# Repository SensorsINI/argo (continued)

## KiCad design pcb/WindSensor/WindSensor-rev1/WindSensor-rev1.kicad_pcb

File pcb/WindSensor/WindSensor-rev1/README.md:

# Argo Wind Sensor - Revision 1

## Overview

This is the first revision (Rev 1) of the Argo Wind Sensor PCB. The board is designed to measure wind speed and direction for the Argo sailboat. 

It is based on Sensiorion reference design (since removed from sensorion because the page could not be migrated). Sensirion kindly supplied the step file as a starting point for the current design. The current design is combined with a mast mounting part that clamps to the mast backstay carbon fiber part.

The PCB design includes 3 SDP32 differential pressure sensors and 
an RGBW LED controller with RGBW LED. Sensors and LED controller are on the Argo I2C bus and are connected to Argo's computer via the 4-wire cable through the Molex SL-series SMD header. The mast mount part includes a set screw to provide strain relief for the SMD Molex header.

The PCB was designed in Kicad 9. The housing was designed in FreeCAD 1.1rc2.

The PCB was fabricated by JLCPCB.

See the argo ROS2 nodes anem.py and mastled.py for sensing and control of the wind sensor.

## Specifications

### Electrical
- **Supply Voltage**: 5V
- **Operating Current**: ~160mA max (3 LEDS, each max 50mA)~
- **Communication Interface**: I2C

### Physical
- **Board Dimensions**: 20x20mm
- **Number of Layers**: 2
- **Surface Finish**: ENIG

## Design Files

This directory contains:
- Schematic files (`.kicad_sch` Kicad Version 9)
- PCB layout files (`.kicad_pcb` )
- 3D models (if applicable)

## Bill of Materials (BOM)

The BOM is generated from Kicad
Parts include datasheet links and Digikey or Farnell part links.

## Manufacturing

### Gerber Files
Gerber files are generated from kicad in the `gerbers/` directory. These can be sent directly to a PCB manufacturer.

### Fabrication Notes
- Minimum trace width: 0.2mm
- Minimum via size: 0.3mm

## Known Issues

- None currently documented for Rev 1

## Revision History

### Rev 1 (Initial Release)
- Initial PCB design
- Date: TBD

### Rev 0 (initial design done by ETH semester student Andrea Mock, ca 2019)

## Contact

For questions or issues related to this PCB design, please contact Tobi Delbruck.

## License

LGPLv3

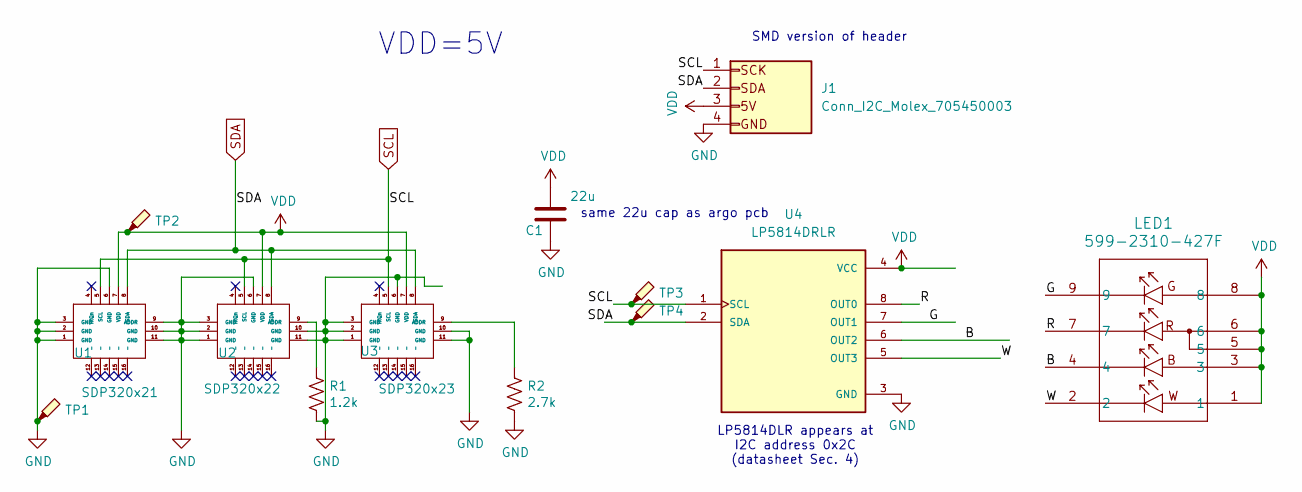
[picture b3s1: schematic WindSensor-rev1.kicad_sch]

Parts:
C1: 22u; C_1210_3225Metric_Pad1.33x2.70mm_HandSolder
J1: Conn_I2C_Molex_705450003; CONN_SD-74099-1000_04_MOL
LED1: 599-2310-427F; 599-2310_DIA_hand_solder
R1: 1.2k; R_0603_1608Metric_Pad0.98x0.95mm_HandSolder
R2: 2.7k; R_0603_1608Metric_Pad0.98x0.95mm_HandSolder
TP1, TP2, TP3, TP4: TestPoint_Probe_autonamed; TestPoint_scope_probe_autonamed
U1: SDP320x21; SDP32
U2: SDP320x22; SDP32
U3: SDP320x23; SDP32
U4: LP5814DRLR; IC_LP5814DRLR_hand_solder; PARTREV MARCH 2025; DigiKey_Part_Number 296-LP5814DRLRCT-ND

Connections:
/B: LED1.4, U4.6 (OUT2)
/G: LED1.9, U4.7 (OUT1)
/R: LED1.7, U4.8 (OUT0)
/W: LED1.2, U4.5 (OUT3)
GND: C1.1, J1.4 (GND), R1.2, R2.2, TP1.1, U1.1 (GND), U1.2 (GND), U1.3 (GND), U1.6 (GND), U1.9 (ADDR), U1.10 (GND), U1.11 (GND), U1.17 (GND), U1.18 (GND), U2.1 (GND), U2.2 (GND), U2.3 (GND), U2.6 (GND), U2.10 (GND), U2.11 (GND), U2.17 (GND), U2.18 (GND), U3.1 (GND), U3.2 (GND), U3.3 (GND), U3.6 (GND), U3.10 (GND), U3.11 (GND), U3.17 (GND), U3.18 (GND), U4.3 (GND)
unnamed: R1.1, U2.9 (ADDR)
unnamed: R2.1, U3.9 (ADDR)
SCL: J1.1 (SCLK), TP3.1, U1.5 (SCL), U2.5 (SCL), U3.5 (SCL), U4.1 (SCL)
SDA: J1.2 (SDA), TP4.1, U1.8 (SDA), U2.8 (SDA), U3.8 (SDA), U4.2 (SDA)
VDD: C1.2, J1.3 (5V), LED1.1, LED1.3, LED1.5, LED1.6, LED1.8, TP2.1, U1.7 (VDD), U2.7 (VDD), U3.7 (VDD), U4.4 (VCC)

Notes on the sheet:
VDD=5V
same 22u cap as argo pcb
LP5814DLR appears at I2C address 0x2C (datasheet Sec. 4)
SMD version of header

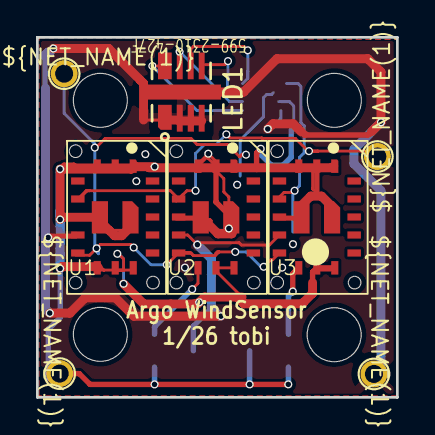
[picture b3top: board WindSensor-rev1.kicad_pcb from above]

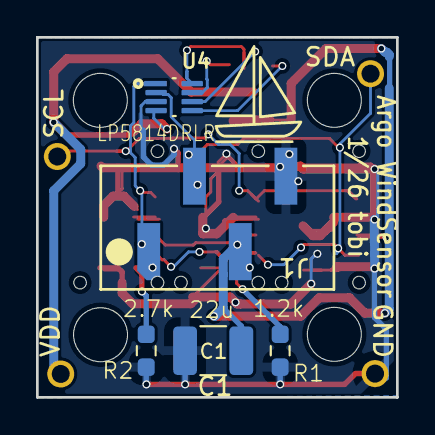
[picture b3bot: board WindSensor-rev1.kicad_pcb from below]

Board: 2 copper layers, 20.0 x 20.0 mm, 17 parts (5 on the bottom side), 10 nets.

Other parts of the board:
H1, H2, H3, H4: (no value)

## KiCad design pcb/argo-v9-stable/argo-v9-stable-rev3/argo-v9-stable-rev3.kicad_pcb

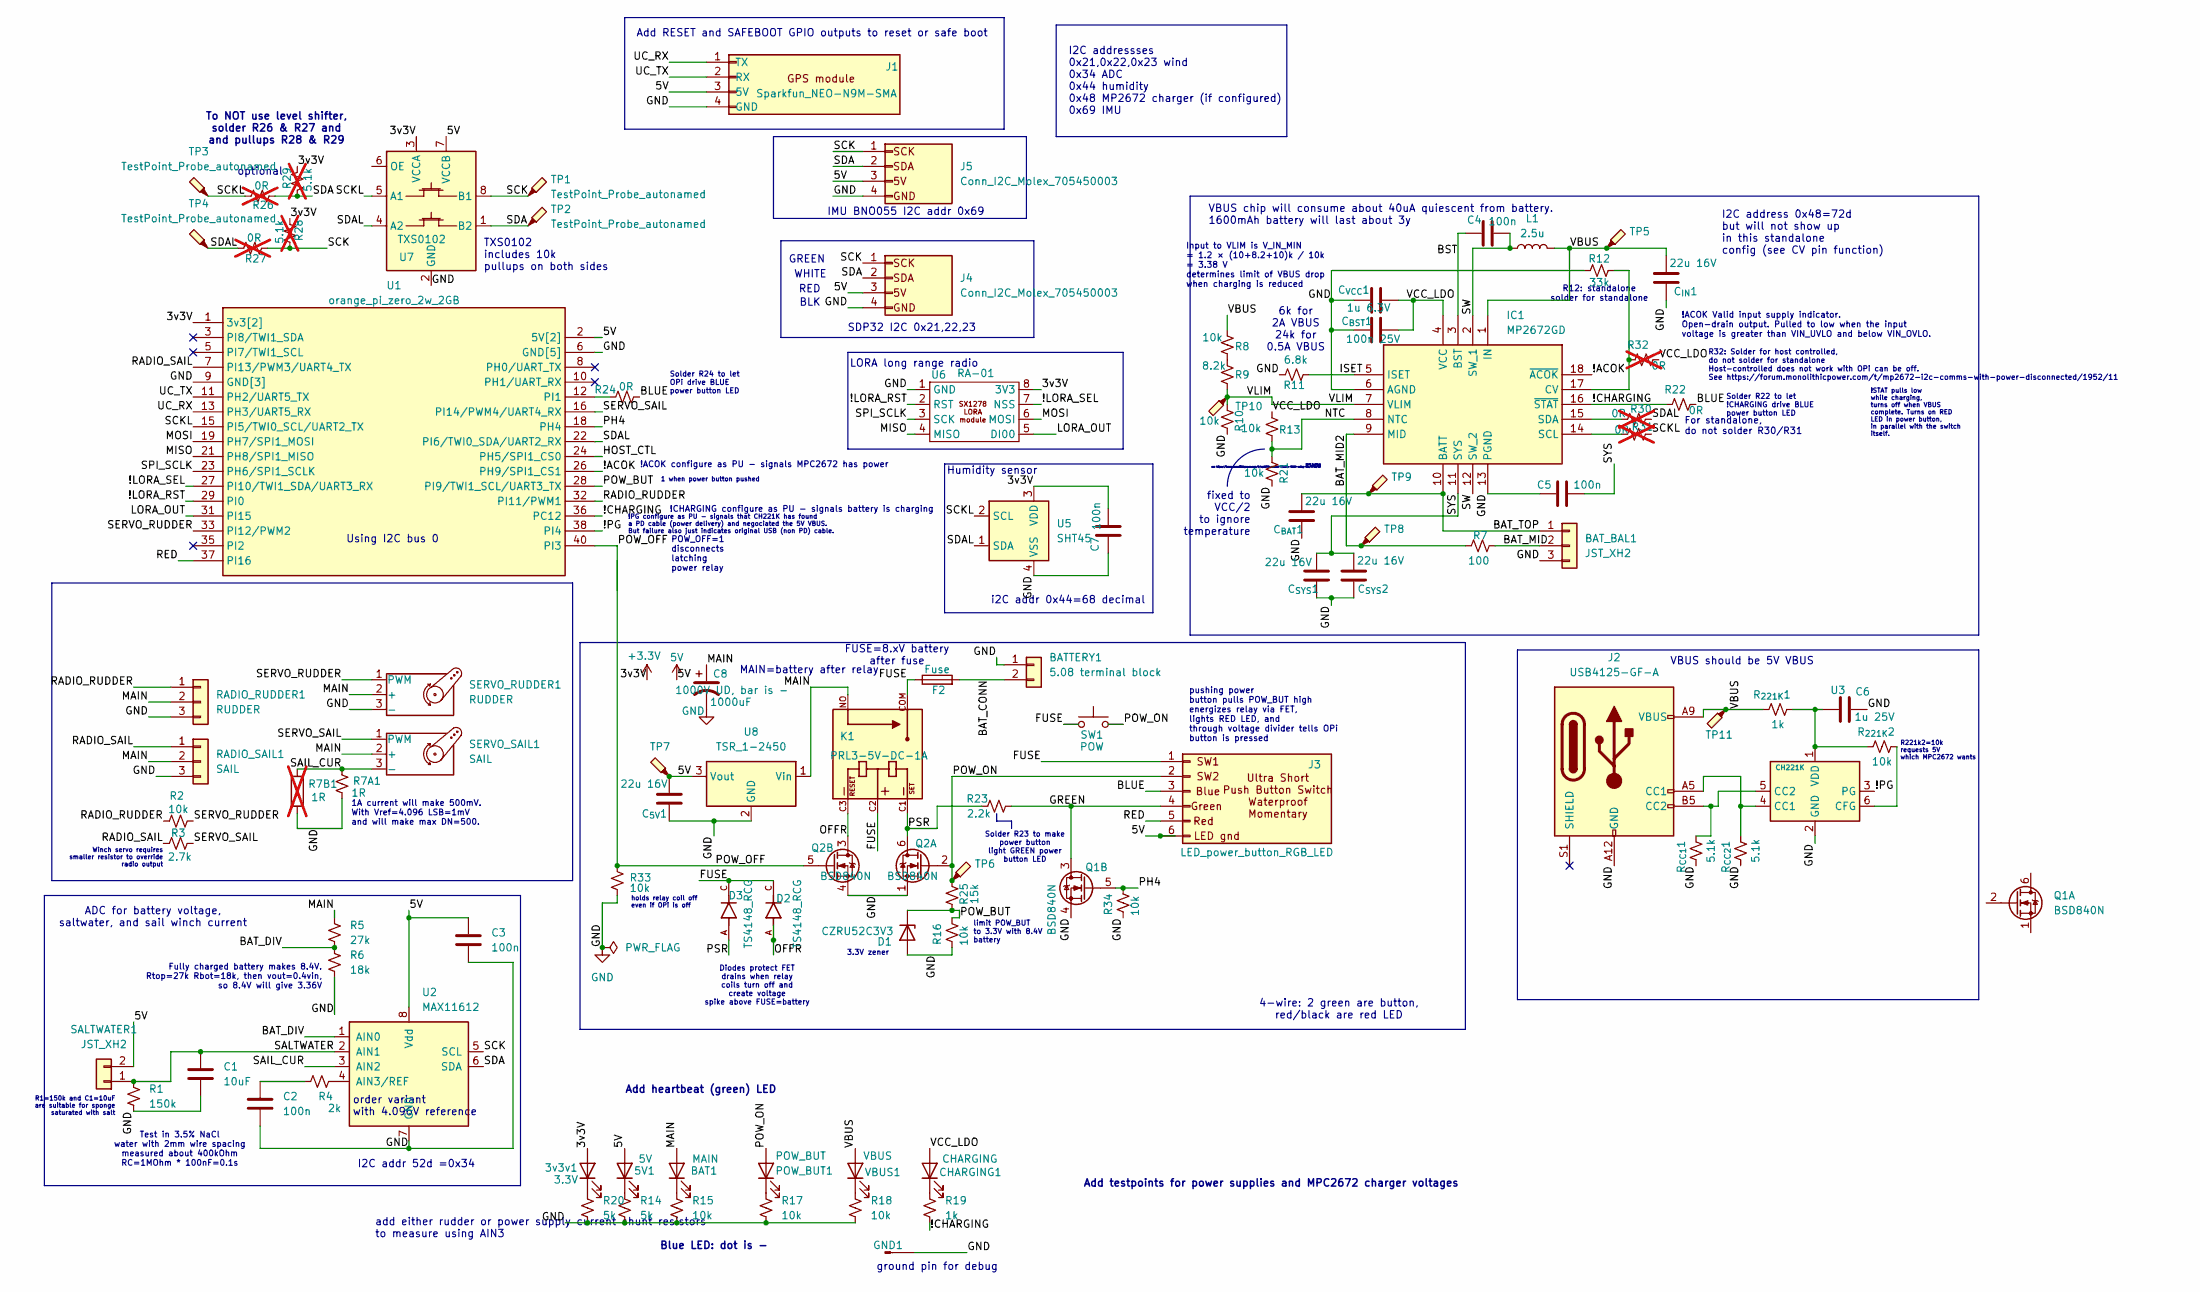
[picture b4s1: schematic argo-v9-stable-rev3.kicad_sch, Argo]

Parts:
3v3v1: 3.3V; LED_0603_1608Metric_Pad1.05x0.95mm_HandSolder
5V1: 5V; LED_0603_1608Metric_Pad1.05x0.95mm_HandSolder
BAT1: MAIN; LED_0603_1608Metric_Pad1.05x0.95mm_HandSolder
BATTERY1: 5.08 terminal block; TerminalBlock_Phoenix_MKDS-1,5-2-5.08_1x02_P5.08mm_Horizont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
BAT_BAL1: JST_XH2; JST_XH_S3B-XH-A-1_1x03_P2.50mm_Horizontal
C1: 10uF; C_0603_1608Metric_Pad1.08x0.95mm_HandSolder
C2, C3, C4, C5, C7: 100n; C_0603_1608Metric_Pad1.08x0.95mm_HandSolder
C6: 1u 25V; C_0603_1608Metric_Pad1.08x0.95mm_HandSolder
C8: 1000uF; PCAP_10x10-ELECT_NCA; digikey have 4 in lab
CHARGING1: CHARGING; LED_0603_1608Metric_Pad1.05x0.95mm_HandSolder
C_{5V}1: 22u 16V; C_1210_3225Metric_Pad1.33x2.70mm_HandSolder
C_{BAT}1: 22u 16V; C_1210_3225Metric_Pad1.33x2.70mm_HandSolder
C_{BST}1: 100n 25V; C_0603_1608Metric_Pad1.08x0.95mm_HandSolder
C_{IN}1: 22u 16V; C_1210_3225Metric_Pad1.33x2.70mm_HandSolder
C_{SYS}1, C_{SYS}2: 22u 16V; C_1210_3225Metric_Pad1.33x2.70mm_HandSolder
C_{VCC}1: 1u 6.3V; C_0603_1608Metric_Pad1.08x0.95mm_HandSolder
D1: CZRU52C3V3; D_0603_1608Metric_hand_solder
D2, D3: TS4148_RCG; DIO_TS4148_RCG; PARTREV A2301
F2: Fuse; Fuse_Smd- Nano SMF AliExp
GND1: Conn_01x01_Pin; Pin_D1.0mm_L10.0mm_LooseFit
IC1: MP2672GD; QFN40P200X300X100-18N-D-handsolder; Manufacturer_Part_Number MP2672GD-0000
J1: Sparkfun_NEO-N9M-SMA; Sparkfun_NEO-M9N-SMA
J2: USB4125-GF-A; USB_C_Receptacle_GCT_USB4125-xx-x-0190_6P_TopMnt_Horizontal
J3: LED_power_button_RGB_LED; JST_XH_S6B-XH-A_1x06_P2.50mm_Horizontal
J4, J5: Conn_I2C_Molex_705450003; I2C_header
K1: PRL3-5V-DC-1A; RELAY_PRL3-5V-DC-1A; PARTREV 1.0
L1: 2.5u; L_Aliexpress_2.5uH
POW_BUT1: POW_BUT; LED_0603_1608Metric_Pad1.05x0.95mm_HandSolder
Q1: BSD840N; SOT-363_SC-70-6
Q2: BSD840N; SOT-363_SC-70-6-handsolder
R1: 150k; R_0603_1608Metric_Pad0.98x0.95mm_HandSolder
R2, R8, R10, R13, R15, R16, R17, R18, R21, R33, R34: 10k; R_0603_1608Metric_Pad0.98x0.95mm_HandSolder
R3: 2.7k; R_0603_1608Metric_Pad0.98x0.95mm_HandSolder
R4: 2k; R_0603_1608Metric_Pad0.98x0.95mm_HandSolder
R5: 27k; R_0603_1608Metric_Pad0.98x0.95mm_HandSolder
R6: 18k; R_0603_1608Metric_Pad0.98x0.95mm_HandSolder
R7: 100; R_0603_1608Metric_Pad0.98x0.95mm_HandSolder
R7A1: 1R; R_0603_1608Metric_Pad0.98x0.95mm_HandSolder
R7B1: 1R; R_Axial_DIN0204_L3.6mm_D1.6mm_P2.54mm_Vertical; not fitted
R9: 8.2k; R_0603_1608Metric_Pad0.98x0.95mm_HandSolder
R11: 6.8k; R_0603_1608Metric_Pad0.98x0.95mm_HandSolder
R12: 33k; R_0603_1608Metric_Pad0.98x0.95mm_HandSolder
R14, R20: 5k; R_0603_1608Metric_Pad0.98x0.95mm_HandSolder
R19: 1k; R_0603_1608Metric_Pad0.98x0.95mm_HandSolder
R22, R24: 0R; R_0603_1608Metric_Pad0.98x0.95mm_HandSolder
R23: 2.2k; R_0603_1608Metric_Pad0.98x0.95mm_HandSolder
R25: 15k; R_0603_1608Metric_Pad0.98x0.95mm_HandSolder
R26, R27, R30, R31, R32: 0R; R_0603_1608Metric_Pad0.98x0.95mm_HandSolder; not fitted
R28, R29: 5.1k; R_0603_1608Metric_Pad0.98x0.95mm_HandSolder; not fitted
RADIO_RUDDER1: RUDDER; PinHeader_1x03_P2.54mm_Vertical
RADIO_SAIL1: SAIL; PinHeader_1x03_P2.54mm_Vertical
R_{221K}1: 1k; R_0603_1608Metric_Pad0.98x0.95mm_HandSolder
R_{221K}2: 10k; R_0603_1608Metric_Pad0.98x0.95mm_HandSolder
R_{CC1}1, R_{CC2}1: 5.1k; R_0603_1608Metric_Pad0.98x0.95mm_HandSolder
SALTWATER1: JST_XH2; JST_XH_S2B-XH-A_1x02_P2.50mm_Horizontal
SERVO_RUDDER1: RUDDER; PinHeader_1x03_P2.54mm_Vertical
SERVO_SAIL1: SAIL; PinHeader_1x03_P2.54mm_Vertical
SW1: POW; SW_Tactile_SPST_NO_Straight_CK_PTS636Sx25SMTRLFS
TP1, TP2, TP3, TP4, TP5, TP6, TP7, TP8, TP9, TP10, TP11: TestPoint_Probe_autonamed; TestPoint_scope_probe_autonamed
U1: orange_pi_zero_2w_2GB; orange_pi_zero_2w_butted
U2: MAX11612; MSOP-8_3x3mm_P0.65mm
U3: CH221K; TSOT-23-6_HandSoldering
U5: SHT45; Sensirion_DFN-4_1.5x1.5mm_P0.8mm_SHT4x_NoCentralPad-handsol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
U6: RA-01; RA-01 SX1278 LORA
U7: TXS0102; SSOP-8_2.95x2.8mm_P0.65mm
U8: TSR_1-2450; Converter_DCDC_TRACO_TSR1-xxxxE_THT
VBUS1: VBUS; LED_0603_1608Metric_Pad1.05x0.95mm_HandSolder

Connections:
5V: 5V1.2 (A), C3.1, C_{5V}1.2, J1.3 (5V), J3.6, J4.3 (5V), J5.3 (5V), SALTWATER1.2, TP7.1, U1.2 (5V[2]), U1.4 (5V[2]), U2.8 (Vdd), U7.7 (VCCB), U8.3 (Vout)
+3.3V: 3v3v1.2 (A), C7.2, R28.2, R29.2, U1.1 (3v3[2]), U1.17 (3v3[2]), U5.3 (VDD), U6.8 (3V3), U7.3 (VCCA)
/!ACOK: IC1.18 (~ACOK), U1.26 (PH9/SPI1_CS1)
/!CHARGING: IC1.16 (~STAT), R19.2, R22.1, U1.36 (PC12)
/!LORA_RST: U1.29 (PI0), U6.2 (RST)
/!LORA_SEL: U1.27 (PI10/TWI1_SDA/UART3_RX), U6.7 (NSS)
/!PG: U1.38 (PI4), U3.3 (PG)
/BAT_CONN: BATTERY1.2, F2.2
/BAT_DIV: R5.2, R6.1, U2.1 (AIN0)
/BAT_MID: BAT_BAL1.2, R7.1
/BAT_MID2: IC1.9 (MID), R7.2, TP8.1
/BAT_TOP: BAT_BAL1.1, C_{BAT}1.2, IC1.10 (BATT), TP9.1
/BLUE: J3.3, R22.2, R24.2
/BST: C4.1, IC1.3 (BST)
/FUSE: D2.C, D3.C, F2.1, J3.1, K1.C2, K1.COM, SW1.1
/GREEN: J3.4, Q1.3 (D), R23.2
/HOST_CTL: U1.24 (PH5/SPI1_CS0)
/LORA_OUT: U1.31 (PI15), U6.5 (DI00)
/MAIN: BAT1.2 (A), C8.1, K1.NO, R5.1, RADIO_RUDDER1.2, RADIO_SAIL1.2, SERVO_RUDDER1.2 (+), SERVO_SAIL1.2 (+), U8.1 (Vin)
/MISO: U1.21 (PH8/SPI1_MISO), U6.4 (MISO)
/MOSI: U1.19 (PH7/SPI1_MOSI), U6.6 (MOSI)
/OFFR: D2.A, K1.C3, Q2.3 (D)
/PH4: Q1.5 (G), R34.2, U1.18 (PH4)
/POW_BUT: D1.1 (K), R16.2, R25.1, U1.28 (PI9/TWI1_SCL/UART3_TX)
/POW_OFF: Q2.5 (G), R33.1, U1.40 (PI3)
/POW_ON: J3.2, POW_BUT1.2 (A), Q2.2 (G), R25.2, SW1.2, TP6.1
/PSR: D3.A, K1.C1, Q2.6 (D), R23.1
/RADIO_RUDDER: R2.1, RADIO_RUDDER1.1, U1.32 (PI11/PWM1)
/RADIO_SAIL: R3.1, RADIO_SAIL1.1, U1.7 (PI13/PWM3/UART4_TX)
/RED: J3.5, U1.37 (PI16)
/SAIL_CUR: R7A1.1, R7B1.1, SERVO_SAIL1.3 (-), U2.3 (AIN2)
/SALTWATER: C1.1, R1.1, SALTWATER1.1, U2.2 (AIN1)
/SCK: J4.1 (SCLK), J5.1 (SCLK), R27.2, R28.1, TP1.1, U2.5 (SCL), U7.8 (B1)
/SCKL: R26.1, R31.2, TP3.1, U1.15 (PI5/TWI0_SCL/UART2_TX), U5.2 (SCL), U7.5 (A1)
/SDA: J4.2 (SDA), J5.2 (SDA), R26.2, R29.1, TP2.1, U2.6 (SDA), U7.1 (B2)
/SDAL: R27.1, R30.2, TP4.1, U1.22 (PI6/TWI0_SDA/UART2_RX), U5.1 (SDA), U7.4 (A2)
/SERVO_RUDDER: R2.2, SERVO_RUDDER1.1 (PWM), U1.33 (PI12/PWM2)
/SERVO_SAIL: R3.2, SERVO_SAIL1.1 (PWM), U1.16 (PI14/PWM4/UART4_RX)
/SPI_SCLK: U1.23 (PH6/SPI1_SCLK), U6.3 (SCK)
/SW: C4.2, IC1.2 (SW_1), IC1.12 (SW_2), L1.1
/SYS: C5.2, C_{SYS}1.2, C_{SYS}2.2, IC1.11 (SYS)
/UC_RX: J1.1 (TX), U1.13 (PH3/UART5_RX)
/UC_TX: J1.2 (RX), U1.11 (PH2/UART5_TX)
/VBUS: C_{IN}1.2, IC1.1 (IN), J2.A9 (VBUS), J2.B9 (VBUS), L1.2, R8.1, R_{221K}1.1, TP5.1, TP11.1, VBUS1.2 (A)
/VCC_LDO: CHARGING1.2 (A), C_{BST}1.2, C_{VCC}1.2, IC1.4 (VCC), R13.1, R32.2
/VLIM: IC1.7 (VLIM), R9.2, R10.1, TP10.1
GND: BATTERY1.1, BAT_BAL1.3, C1.2, C2.2, C3.2, C5.1, C6.2, C7.1, C8.2, C_{5V}1.1, C_{BAT}1.1, C_{BST}1.1, C_{IN}1.1, C_{SYS}1.1, C_{SYS}2.1, C_{VCC}1.1, D1.2 (A), GND1.1, IC1.6 (AGND), IC1.13 (PGND), J1.4 (GND), J2.A12 (GND), J2.B12 (GND), J4.4 (GND), J5.4 (GND), Q1.4 (S), Q2.1 (S), Q2.4 (S), R1.2, R6.2, R7A1.2, R7B1.2, R10.2, R11.1, R12.2, R14.2, R15.2, R16.1, R17.2, R18.2, R20.2, R21.2, R33.2, R34.1, RADIO_RUDDER1.3, RADIO_SAIL1.3, R_{CC1}1.1, R_{CC2}1.1, SERVO_RUDDER1.3 (-), U1.6 (GND[5]), U1.9 (GND[3]), U1.14 (GND[5]), U1.20 (GND[5]), U1.25 (GND[3]), U1.30 (GND[5]), U1.34 (GND[5]), U1.39 (GND[3]), U2.7 (GND), U3.2 (GND), U5.4 (VSS), U6.1 (GND), U7.2 (GND), U8.2 (GND)
unnamed: 3v3v1.1 (K), R20.1
unnamed: 5V1.1 (K), R14.1
unnamed: BAT1.1 (K), R15.1
unnamed: C2.1, R4.2
unnamed: CHARGING1.1 (K), R19.1
unnamed: IC1.17 (CV), R12.1, R32.1
unnamed: IC1.5 (ISET), R11.2
unnamed: IC1.8 (NTC), R13.2, R21.1
unnamed: IC1.14 (SCL), R31.1
unnamed: IC1.15 (SDA), R30.1
unnamed: J2.A5 (CC1), R_{CC2}1.2, U3.4 (CC1)
unnamed: J2.B5 (CC2), R_{CC1}1.2, U3.5 (CC2)
unnamed: POW_BUT1.1 (K), R17.1
unnamed: R8.2, R9.1
unnamed: R24.1, U1.12 (PI1)
unnamed: R4.1, U2.4 (AIN3/REF)
unnamed: R_{221K}2.2, U3.6 (CFG)
unnamed: C6.1, R_{221K}1.2, R_{221K}2.1, U3.1 (VDD)
unnamed: R18.1, VBUS1.1 (K)

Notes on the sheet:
optional
Add testpoints for power supplies and MPC2672 charger voltages
ground pin for debug
Add RESET and SAFEBOOT GPIO outputs to reset or safe boot
GREEN
!PG configure as PU - signals that CH221K has found a PD cable (power delivery) and negociated the 5V VBUS. But failure also just indicates original USB (non PD) cable.
add either rudder or power supply current shunt resistors to measure using AIN3
FUSE=8.xV battery after fuse
6k for 2A VBUS 24k for 0.5A VBUS
TXS0102 includes 10k pullups on both sides
R221k2=10k requests 5V which MPC2672 wants
To NOT use level shifter, solder R26 & R27 and and pullups R28 & R29
pushing power button pulls POW_BUT high energizes relay via FET, lights RED LED, and through voltage divider tells OPi button is pressed
1A current will make 500mV. With Vref=4.096 LSB=1mV and will make max DN=500.
Input to VLIM is V_IN_MIN = 1.2 × (10+8.2+10)k / 10k = 3.38 V determines limit of VBUS drop when charging is reduced
Fully charged battery makes 8.4V. Rtop=27k Rbot=18k, then vout=0.4vin, so 8.4V will give 3.36V
Solder R23 to make power button light GREEN power button LED
fixed to VCC/2 to ignore temperature
Winch servo requires smaller resistor to override radio output
holds relay coil off even if OPi is off
I2C address 0x48=72d but will not show up in this standalone config (see CV pin function)
I2C addr 52d =0x34
IMU BNO055 I2C addr 0x69
i2C addr 0x44=68 decimal
!ACOK Valid input supply indicator. Open-drain output. Pulled to low when the input voltage is greater than VIN_UVLO and below VIN_OVLO.
MAIN=battery after relay
BLK
!ACOK configure as PU - signals MPC2672 has power
WHITE
!CHARGING configure as PU - signals battery is charging
R32: Solder for host controlled, do not solder for standalone Host-controlled does not work with OPi can be off. See https://forum.monolithicpower.com/t/mp2672-i2c-comms-with-power-disconnected/1952/11
ADC for battery voltage, saltwater, and sail winch current
Solder R24 to let OPi drive BLUE power button LED
POW_OFF=1 disconnects latching power relay
Humidity sensor
R12: standalone solder for standalone
I2C addressses 0x21,0x22,0x23 wind 0x34 ADC 0x44 humidity 0x48 MP2672 charger (if configured) 0x69 IMU
For standalone, do not solder R30/R31
1 when power button pushed
VBUS should be 5V VBUS

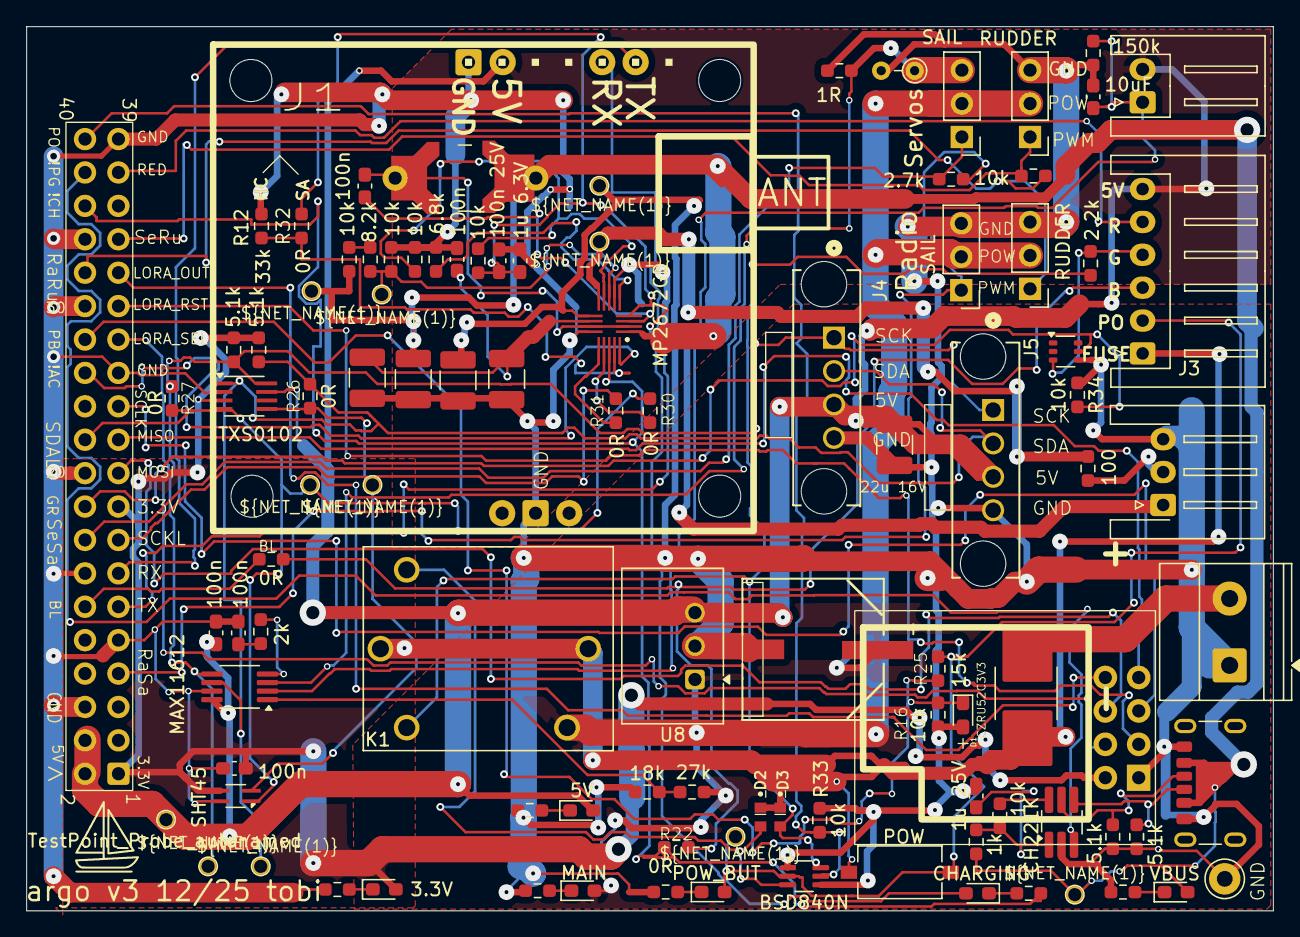
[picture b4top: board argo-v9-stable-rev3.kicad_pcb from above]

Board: 2 copper layers, 94.8 x 67.2 mm, 102 parts (0 on the bottom side), 65 nets.

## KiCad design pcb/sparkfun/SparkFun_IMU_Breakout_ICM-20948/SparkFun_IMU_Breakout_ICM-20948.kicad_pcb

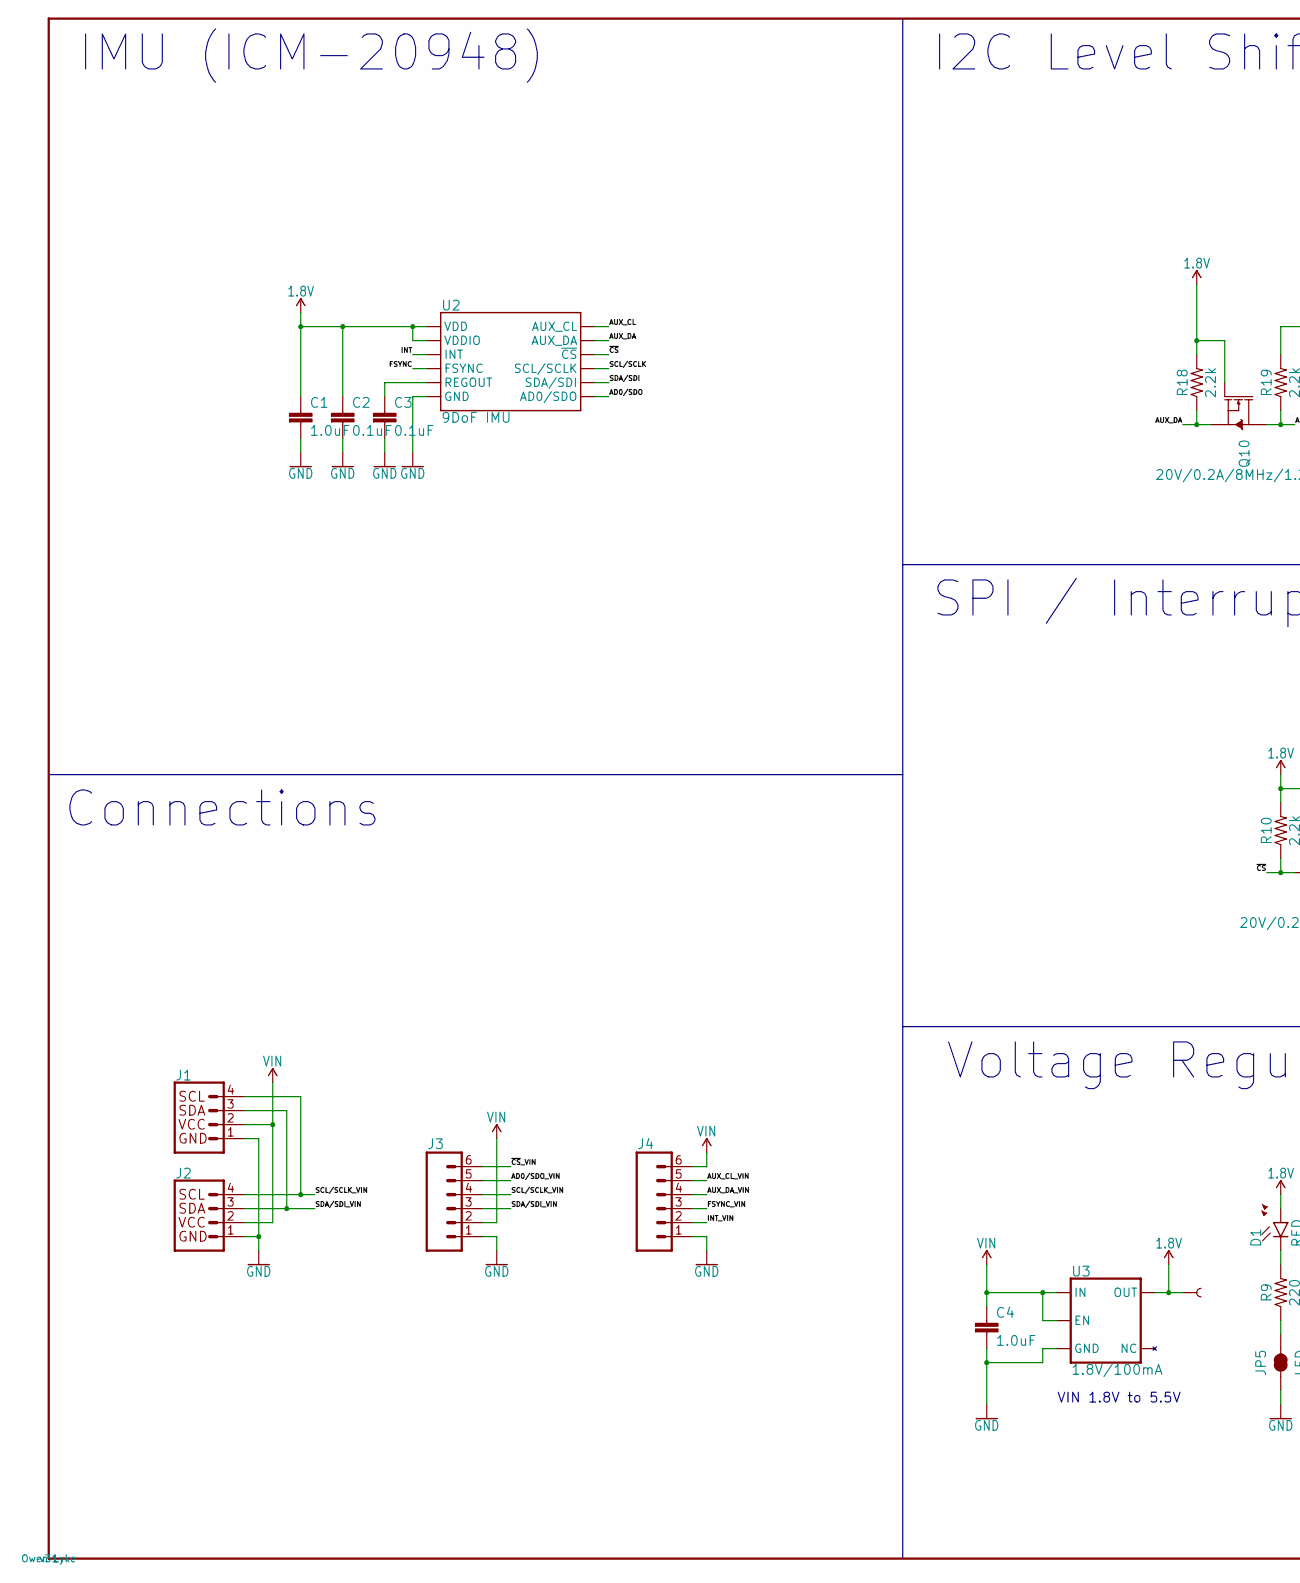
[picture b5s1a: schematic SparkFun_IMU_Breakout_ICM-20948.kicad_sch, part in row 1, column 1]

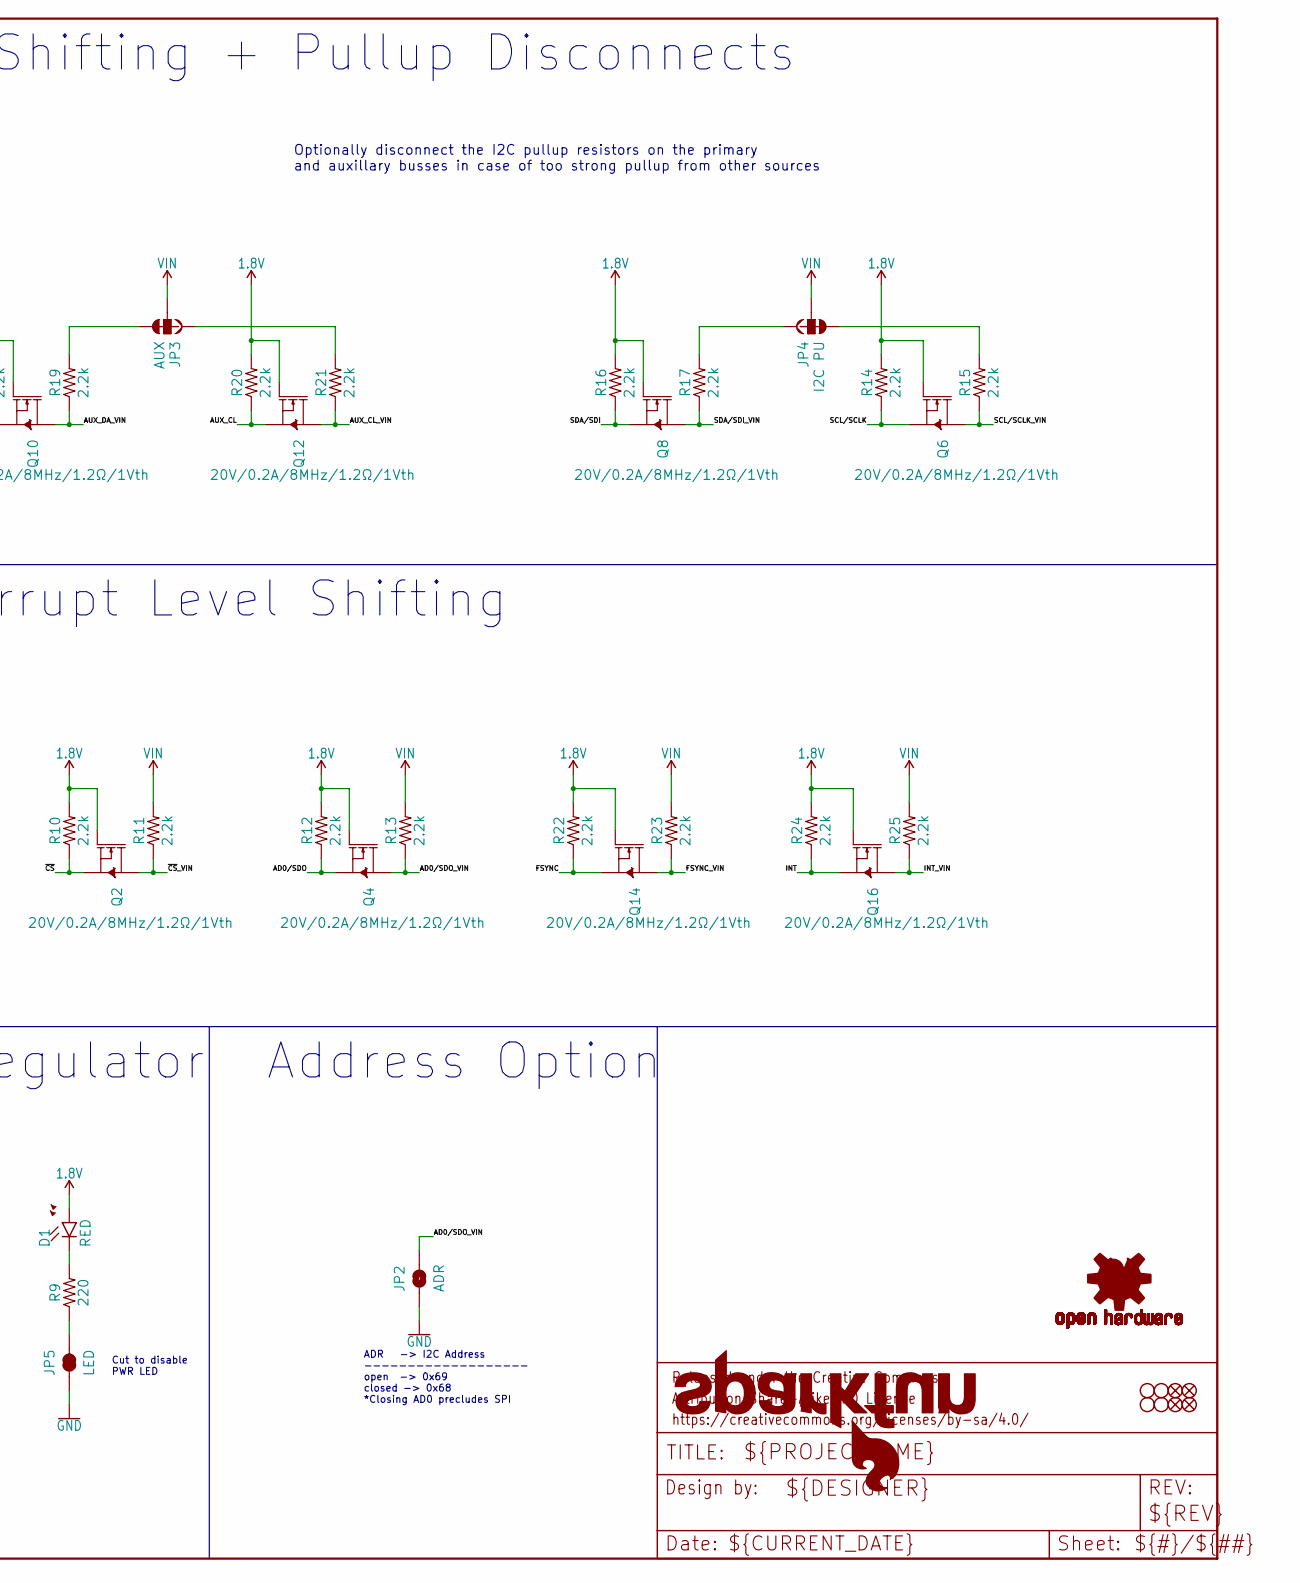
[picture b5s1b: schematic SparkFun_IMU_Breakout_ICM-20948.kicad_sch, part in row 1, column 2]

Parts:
C1, C4: 1.0uF; 0603
C2, C3: 0.1uF; 0603
D1: RED; LED-0603
FD1, FD2, FD3, FD4: FIDUCIAL1X2; FIDUCIAL-1X2
FRAME2: FRAME-LEDGER; CREATIVE_COMMONS
H1, H2, H3, H4: STAND-OFF
J1, J2: QWIIC_CONNECTORJS-1MM; JST04_1MM_RA
J3, J4: CONN_06NO_SILK_NO_POP; 1X06_NO_SILK
JP2: ADR; SMT-JUMPER_2_NO_SILK
JP3: AUX; SMT-JUMPER_3_2-NC_TRACE_SILK
JP4: I2C PU; SMT-JUMPER_3_2-NC_TRACE_SILK
JP5: LED; SMT-JUMPER_2_NC_TRACE_SILK
LOGO1: SFE_LOGO_NAME_FLAME.1_INCH; SFE_LOGO_NAME_FLAME_.1
LOGO2: OSHW-LOGOMINI; OSHW-LOGO-MINI
Q2, Q4, Q6, Q8, Q10, Q12, Q14, Q16: 20V/0.2A/8MHz/1.2Ω/1Vth; SOT-416FL
R9: 220; 0603
R10, R11, R12, R13, R14, R15, R16, R17, R18, R19, R20, R21, R22, R23, R24, R25: 2.2k; 0402-TIGHT
TP1: 1.8V; PAD.03X.03
U2: 9DoF IMU; QFN24-3X3
U3: 1.8V/100mA; SC70

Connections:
1.8V: C1.1, C2.1, D1.A, Q2.1 (G), Q4.1 (G), Q6.1 (G), Q8.1 (G), Q10.1 (G), Q12.1 (G), Q14.1 (G), Q16.1 (G), R10.2, R12.2, R14.2, R16.2, R18.2, R20.2, R22.2, R24.2, TP1.P$1, U2.8 (VDDIO), U2.13 (VDD), U3.5 (OUT)
AD0/SDO: Q4.2 (S), R12.1, U2.9 (AD0/SDO)
AD0/SDO_VIN: J3.5, JP2.2, Q4.3 (D), R13.1
AUX_CL: Q12.2 (S), R20.1, U2.7 (AUX_CL)
AUX_CL_VIN: J4.5, Q12.3 (D), R21.1
AUX_DA: Q10.2 (S), R18.1, U2.21 (AUX_DA)
AUX_DA_VIN: J4.4, Q10.3 (D), R19.1
FSYNC: Q14.2 (S), R22.1, U2.11 (FSYNC)
FSYNC_VIN: J4.3, Q14.3 (D), R23.1
GND: C1.2, C2.2, C3.2, C4.2, J1.1, J2.1, J3.1, J4.1, JP2.1, JP5.1, U2.18 (GND), U2.20 (GND), U3.2 (GND)
INT: Q16.2 (S), R24.1, U2.12 (INT)
INT_VIN: J4.2, Q16.3 (D), R25.1
unnamed: C3.1, U2.10 (REGOUT)
unnamed: JP4.3, R15.2
unnamed: JP4.1, R17.2
unnamed: JP3.1, R21.2
unnamed: JP3.3, R19.2
unnamed: D1.C, R9.2
unnamed: JP5.2, R9.1
SCL/SCLK: Q6.2 (S), R14.1, U2.23 (SCL/SCLK)
SCL/SCLK_VIN: J1.4, J2.4, J3.4, Q6.3 (D), R15.1
SDA/SDI: Q8.2 (S), R16.1, U2.24 (SDA/SDI)
SDA/SDI_VIN: J1.3, J2.3, J3.3, Q8.3 (D), R17.1
VIN: C4.1, J1.2, J2.2, J3.2, J4.6, JP3.2, JP4.2, R11.2, R13.2, R23.2, R25.2, U3.1 (IN), U3.3 (EN)
~CS: Q2.2 (S), R10.1, U2.22 (~CS)
~CS_VIN: J3.6, Q2.3 (D), R11.1

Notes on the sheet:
ADR -> I2C Address ------------------- open -> 0x69 closed -> 0x68 *Closing AD0 precludes SPI
Voltage Regulator
Cut to disable PWR LED
Connections
VIN 1.8V to 5.5V
Address Option
SPI / Interrupt Level Shifting
I2C Level Shifting + Pullup Disconnects
IMU (ICM-20948)
Optionally disconnect the I2C pullup resistors on the primary and auxillary busses in case of too strong pullup from other sources

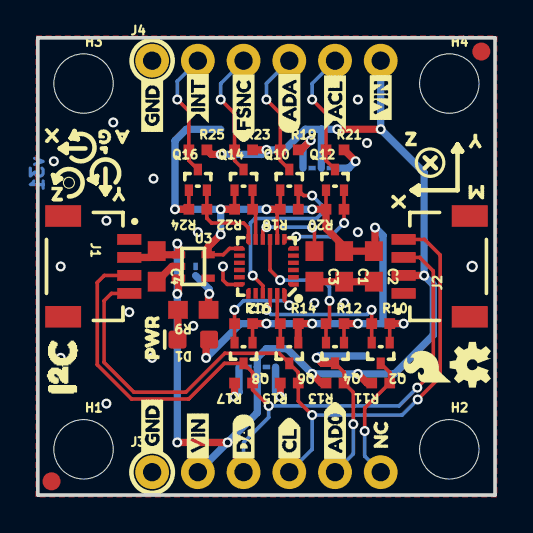
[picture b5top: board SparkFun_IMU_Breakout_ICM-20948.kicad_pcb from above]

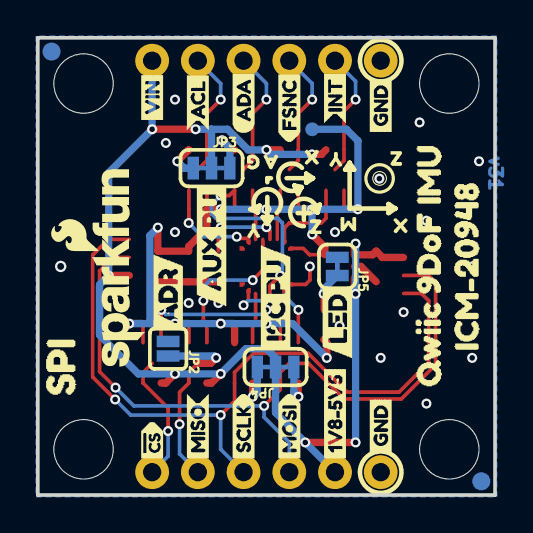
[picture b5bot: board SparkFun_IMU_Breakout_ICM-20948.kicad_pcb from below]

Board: 2 copper layers, 25.4 x 25.4 mm, 104 parts (36 on the bottom side), 26 nets.

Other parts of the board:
U$1, U$2, U$22, U$24: GND4
U$3: PWR0
U$4, U$21: INT3
U$5, U$20: FSNC2
U$6, U$19: ACL1
U$7, U$18: ADA0
U$8: MISO13
U$9: MOSI14
U$10: SCLK15
U$11: #CS16
U$12: 1V8#5V57
U$13, U$30, U$44: VIN5
U$14: NC17
U$15: CL4
U$16: DA2
U$17: AD012
U$23: ADR2
U$25: I2C_PU21
U$26: SPI19
U$27: AUX_PU24
U$28: SFE_LOGO_FLAME_.1
U$29: LED23
U$31: ICM#2094820
U$34, U$40, U$50, U$57: X0
U$35, U$41, U$51, U$58: Y1
U$36, U$42, U$52, U$59: Z2
U$37, U$60: G5
U$38, U$61: A4
U$39, U$49: M3
U$43: QWIIC_9DOF_IMU_0
U$45: I#C1
